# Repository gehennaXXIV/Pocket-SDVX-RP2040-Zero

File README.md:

# Pocket-SDVX-RP2040-Zero

This work is licensed under a [Creative Commons Attribution-NonCommercial-ShareAlike 4.0 International License](https://creativecommons.org/licenses/by-nc-sa/4.0/).  
中国人，我在看你们。

## Changes from the original
- Removed LEDs and SMD parts for a simpler, lower-cost hand-solder build  
- Replaced the Pi Pico with an RP2040 Zero  
- Changed plate screws from M3 to M2 (using round spacers + rubber adhesive feet)  
- Switched from plate-mount to PCB-mount stabilizers  

---

## Parts Required
- **JLCPCB boards** (180 × 100 mm, white, remove order number or specify location):  
  - 1× Pocket-SDVX-RP2040-Zero-Plate (MOQ 5)  
  - 1× Pocket-SDVX-RP2040-Zero (MOQ 5)  
- 1× RP2040 Zero  
- 1× 6×6×7 mm tactile switch (4-pin)  
- 2× Encoder – [PEC16-4015F-N0024](https://www.speedylabs.us/product/bourns-pec16-2015f-n0024-encoder/) (or any EC16 encoder with no detents)  
- 4× 1206 10nF SMD capacitors  
- 7× Any MX switches  
- 7× Gateron hotswap sockets  

## 
- 1× 3D-printed case  
- 4× M2×10mm round standoffs (aligns plate with 3DP case + USB port)  
- 8× M2×6mm screws  
- 4× M3×5mm round acrylic spacers (7×3×5 mm tall, prevents PCB sag)  
- 2× 2U PCB-mount stabilizers (screw-in preferred)  
- 4× adhesive rubber feet  
- 1x optional 1.5mm clear acrylic top cutout

- XDA Keycap Set: https://www.speedylabs.us/product/pocket-sdvx-keycaps/  
  - 1× 1u  
  - 4× 1.5u  
  - 2× 2u  
- 2× 22 mm knobs: https://www.speedylabs.us/product/pocket-sdvx-aluminum-knob/  

---

## Assembly Notes
The RP2040 Zero is soldered from below the PCB, with the buttons facing upward.

## Flashing the Firmware to RP2040 Zero

**Firmware to use:** [Download here](https://github.com/gehennaXXIV/Pico-Game-Controller/actions/runs/18122910987/artifacts/4140737036)

---

1. **Download** the firmware `.zip` file from the link above.  
2. **Extract** the `.uf2` file from the zip archive.  
3. On your RP2040 Zero, **press and hold** the **BOOT** button.  
4. While holding the button, **connect** the board to your computer via USB.  
5. The RP2040 Zero will appear as a **USB drive** on your computer.  
6. **Drag and drop** the `.uf2` firmware file onto the RP2040 Zero drive.  
7. The board will automatically reboot and run the new firmware.  

---

## Attribution
This project is a remix of [Pocket-SDVX-Pico-v4](https://github.com/speedypotato/Pocket-SDVX-Pico-v4) by **speedypotato**, licensed under [CC BY-NC-SA 4.0](https://creativecommons.org/licenses/by-nc-sa/4.0/).  

It is released under the same license.

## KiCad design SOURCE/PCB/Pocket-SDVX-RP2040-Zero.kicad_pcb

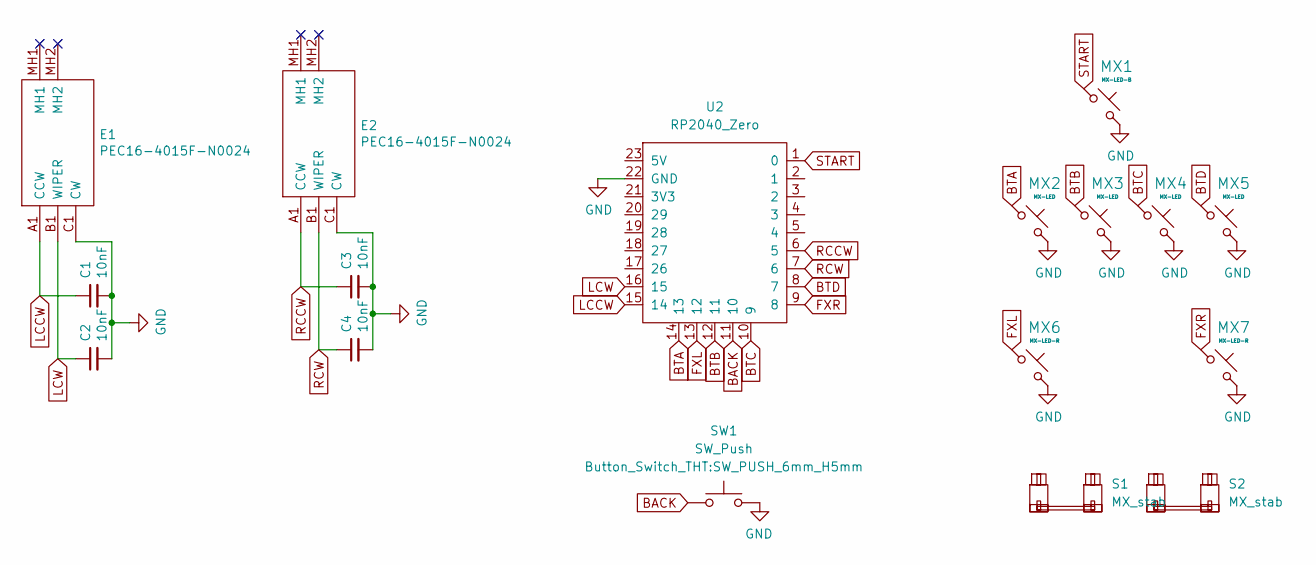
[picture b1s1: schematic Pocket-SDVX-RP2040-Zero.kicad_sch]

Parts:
C1, C2, C3, C4: 10nF; C_1206_3216Metric_Pad1.33x1.80mm_HandSolder; LCSC C57112
E1, E2: PEC16-4015F-N0024; PEC16-4015F-N0024-millmax; Mouser Part Number 652-PEC16-4015FN0024
MX1: MX-LED-B; SW_MX_HS_CPG151101S11_1u; LCSC C440444
MX2, MX3, MX4, MX5: MX-LED; SW_MX_HS_CPG151101S11_1.5u; LCSC C26545
MX6, MX7: MX-LED-R; SW_MX_HS_CPG151101S11_1u; LCSC C440441
S1, S2: MX_stab; STAB_MX_P_2u
SW1: SW_Push; SW_PUSH_6mm_H5mm
U2: RP2040_Zero

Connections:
BACK: SW1.1, U2.11 (10)
BTA: MX2.1, U2.14 (13)
BTB: MX3.1, U2.12 (11)
BTC: MX4.1, U2.10 (9)
BTD: MX5.1, U2.8 (7)
FXL: MX6.1, U2.13 (12)
FXR: MX7.1, U2.9 (8)
GND: C1.2, C2.2, C3.2, C4.2, E1.C1 (CW), E2.C1 (CW), MX1.2, MX2.2, MX3.2, MX4.2, MX5.2, MX6.2, MX7.2, SW1.2, U2.22 (GND)
LCCW: C1.1, E1.A1 (CCW), U2.15 (14)
LCW: C2.1, E1.B1 (WIPER), U2.16 (15)
RCCW: C3.1, E2.A1 (CCW), U2.6 (5)
RCW: C4.1, E2.B1 (WIPER), U2.7 (6)
START: MX1.1, U2.1 (0)

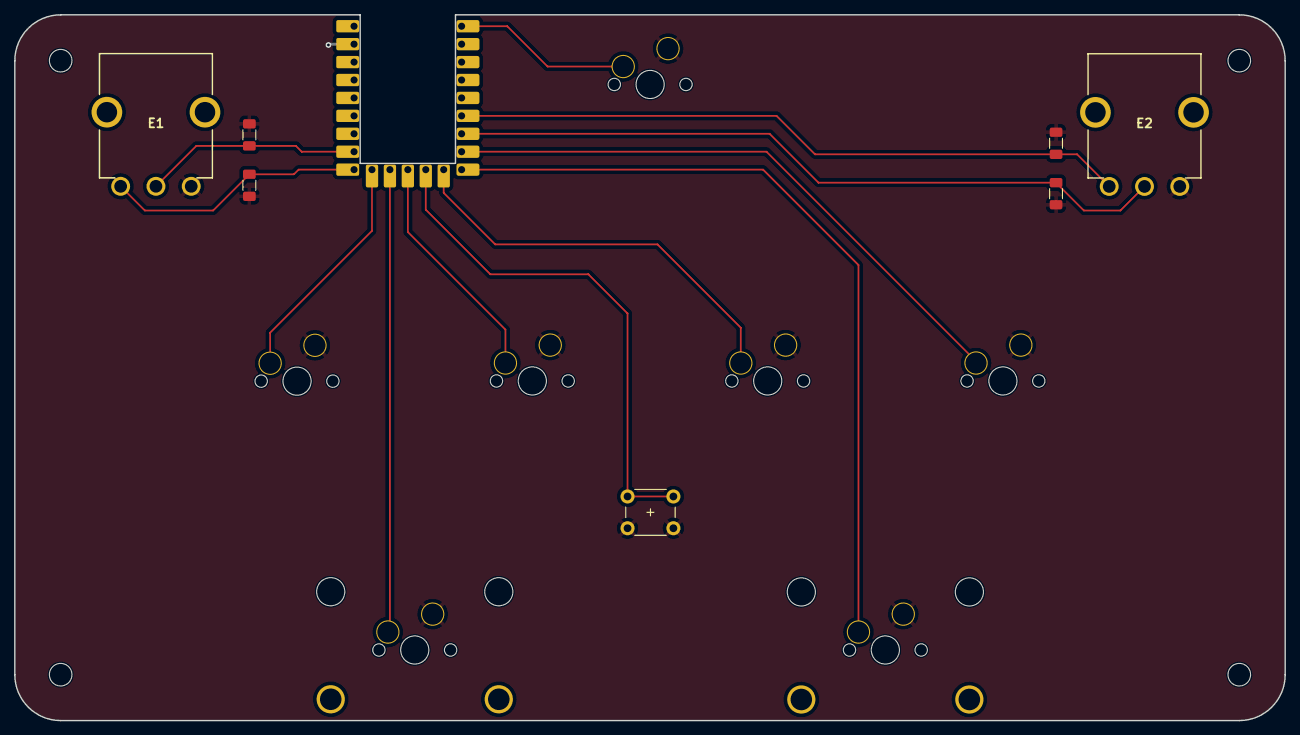
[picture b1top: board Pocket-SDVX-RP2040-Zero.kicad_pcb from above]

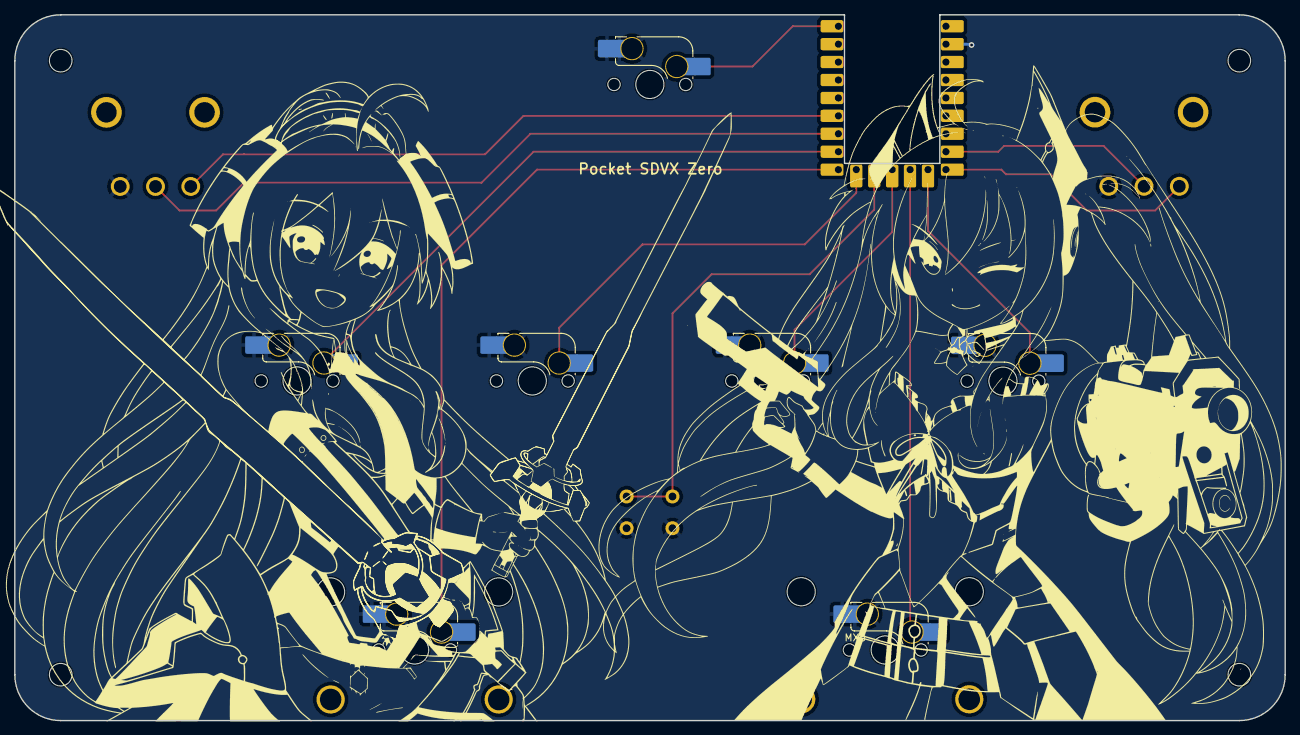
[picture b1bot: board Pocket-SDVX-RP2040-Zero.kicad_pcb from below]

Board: 2 copper layers, 180.0 x 100.0 mm, 17 parts (7 on the bottom side), 13 nets.

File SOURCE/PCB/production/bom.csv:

Designator,Footprint,Quantity,Value,LCSC Part #
"C1, C2, C3, C4",1206,4,10nF,C57112
"E1, E2",PEC16-4015F-N0024-millmax,2,PEC16-4015F-N0024,
MX1,SW_MX_HS_CPG151101S11_1u,1,MX-LED-B,C440444
"MX2, MX3, MX4, MX5",SW_MX_HS_CPG151101S11_1.5u,4,MX-LED,C26545
"MX6, MX7",SW_MX_HS_CPG151101S11_1u,2,MX-LED-R,C440441
"S1, S2",STAB_MX_P_2u,2,MX_stab,
SW1,SW_PUSH_6mm_H5mm,1,SW_Push,
U2,RP2040_Zero,1,RP2040_Zero,

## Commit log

2025-09-15 clone
